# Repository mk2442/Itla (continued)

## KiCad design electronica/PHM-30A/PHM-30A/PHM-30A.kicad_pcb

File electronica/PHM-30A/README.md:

# PHM-30A
Puente H con Mosfet discretos 30A

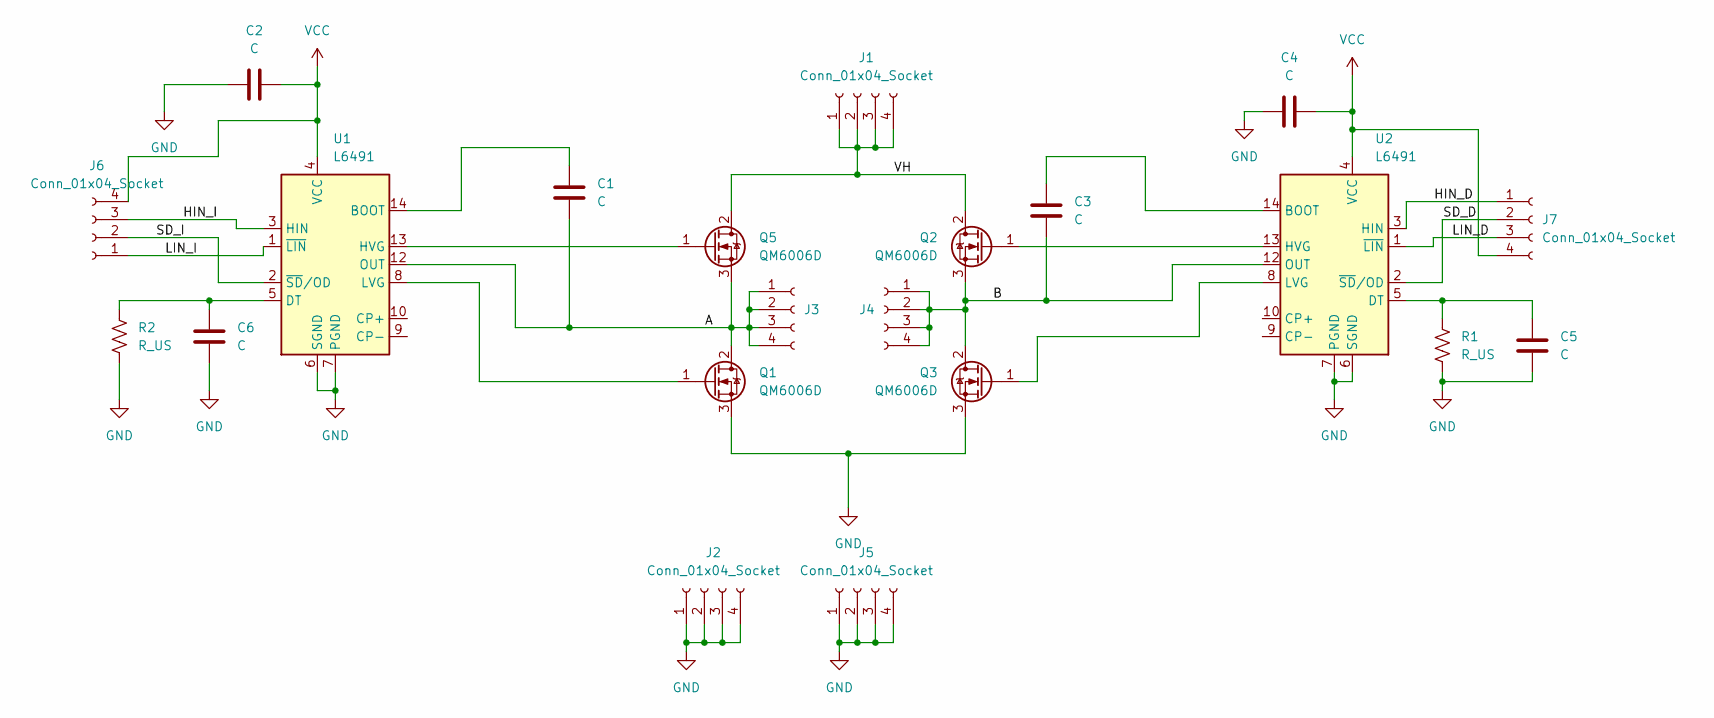
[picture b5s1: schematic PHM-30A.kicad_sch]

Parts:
C1, C2, C3, C4: C; C_0805_2012Metric
C5, C6: C; C_0603_1608Metric
J1, J2, J3, J4, J5, J6, J7: Conn_01x04_Socket; PinSocket_1x04_P1.27mm_Castellated
Q1, Q2, Q3, Q5: QM6006D; TO-252-2
R1, R2: R_US; R_0603_1608Metric
U1, U2: L6491; SO-14_3.9x8.65mm_P1.27mm

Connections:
/A: C1.2, J3.1, J3.2, J3.3, J3.4, Q1.2 (D), Q5.3 (S), U1.12 (OUT)
/B: C3.2, J4.1, J4.2, J4.3, J4.4, Q2.3 (S), Q3.2 (D), U2.12 (OUT)
/HIN_D: J7.1, U2.3 (HIN)
/HIN_I: J6.3, U1.3 (HIN)
/LIN_D: J7.3, U2.1 (~LIN)
/LIN_I: J6.1, U1.1 (~LIN)
/SD_D: J7.2, U2.2 (~SD/OD)
/SD_I: J6.2, U1.2 (~SD/OD)
/VH: J1.1, J1.2, J1.3, J1.4, Q2.2 (D), Q5.2 (D)
GND: C2.2, C4.1, C5.1, C6.1, J2.1, J2.2, J2.3, J2.4, J5.1, J5.2, J5.3, J5.4, Q1.3 (S), Q3.3 (S), R1.2, R2.2, U1.6 (SGND), U1.7 (PGND), U2.6 (SGND), U2.7 (PGND)
unnamed: Q1.1 (G), U1.8 (LVG)
unnamed: Q2.1 (G), U2.13 (HVG)
unnamed: Q3.1 (G), U2.8 (LVG)
unnamed: Q5.1 (G), U1.13 (HVG)
unnamed: C1.1, U1.14 (BOOT)
unnamed: C6.2, R2.1, U1.5 (DT)
unnamed: C3.1, U2.14 (BOOT)
unnamed: C5.2, R1.1, U2.5 (DT)
VCC: C2.1, C4.2, J6.4, J7.4, U1.4 (VCC), U2.4 (VCC)

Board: 2 copper layers, 21 parts (0 on the bottom side), 19 nets, no tracks yet.

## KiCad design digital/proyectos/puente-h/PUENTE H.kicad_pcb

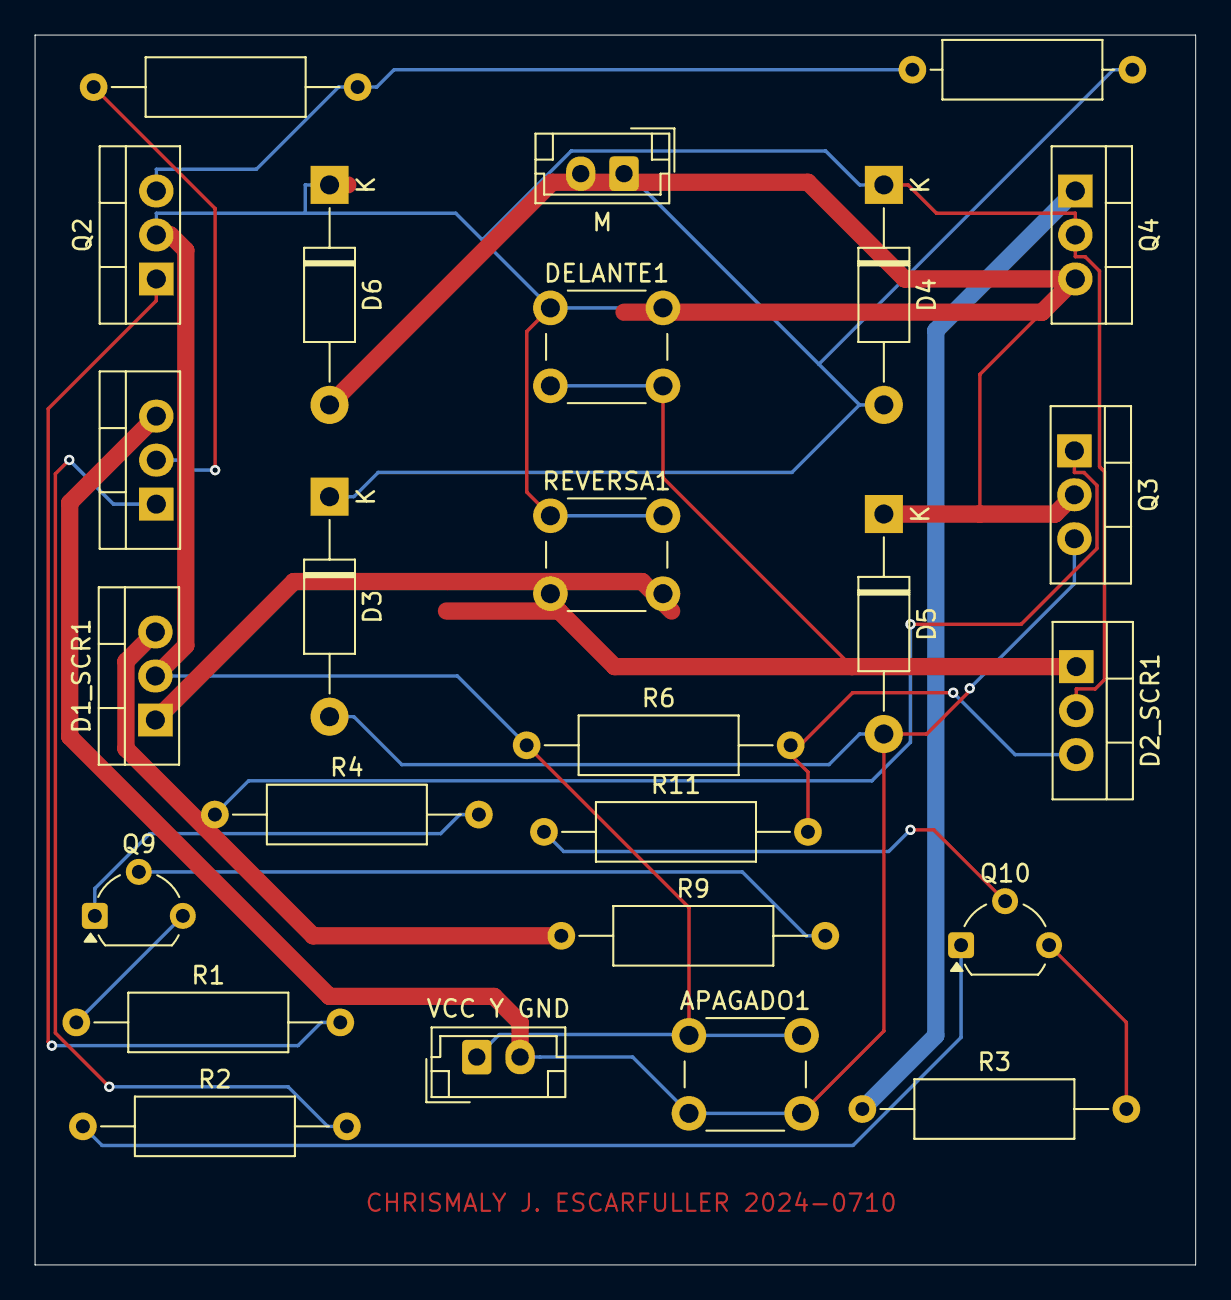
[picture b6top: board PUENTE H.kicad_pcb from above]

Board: 2 copper layers, 67.0 x 71.0 mm, 26 parts (0 on the bottom side), 20 nets.

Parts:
APAGADO1: SW_Push; SW_PUSH_6mm_H7.3mm
D1_SCR1, D2_SCR1: Q_SCR_GAK; TO-220-3_Vertical
D3, D4, D5, D6: 1N4007; D_DO-41_SOD81_P12.70mm_Horizontal
DELANTE1: SW_Push; SW_PUSH_6mm_H7.3mm
M: Screw_Terminal_01x02; JST_EH_B2B-EH-A_1x02_P2.50mm_Vertical
Q1, Q2, Q3, Q4: TIP41; TO-220-3_Vertical
Q9, Q10: 2N3904; TO-92L_Wide
R1, R2, R3, R4, R6, R9, R11: R; R_Axial_DIN0309_L9.0mm_D3.2mm_P15.24mm_Horizontal
REVERSA1: SW_Push; SW_PUSH_6mm_H7.3mm
VCC Y GND: Screw_Terminal_01x02; JST_EH_B2B-EH-A_1x02_P2.50mm_Vertical
jUMPER1: R; R_Axial_DIN0309_L9.0mm_D3.2mm_P12.70mm_Horizontal
jUMPER2: R; R_Axial_DIN0309_L9.0mm_D3.2mm_P15.24mm_Horizontal

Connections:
GNDPWR: APAGADO1.2, D3.2 (A), D5.2 (A), Q1.3 (E), Q3.3 (E), VCC Y GND.2
unnamed: D1_SCR1.1 (G), REVERSA1.2
unnamed: D1_SCR1.3 (K), R9.1
unnamed: D2_SCR1.1 (G), DELANTE1.2
unnamed: D2_SCR1.3 (K), R6.2, R11.2
unnamed: D3.1 (K), D4.2 (A), M.1, jUMPER1.2
unnamed: D5.1 (K), D6.2 (A), M.2, Q3.2 (C), Q4.3 (E)
unnamed: Q1.1 (B), R2.2
unnamed: Q1.2 (C), jUMPER2.1
unnamed: Q2.1 (B), R1.2
unnamed: Q2.3 (E), jUMPER1.1, jUMPER2.2
unnamed: Q3.1 (B), R4.1
unnamed: Q4.1 (B), R3.1
unnamed: Q9.2 (B), R9.2
unnamed: Q9.3 (C), R1.1
unnamed: Q9.1 (E), R4.2
unnamed: Q10.2 (B), R11.1
unnamed: Q10.3 (C), R3.2
unnamed: Q10.1 (E), R2.1
VCC: APAGADO1.1, D1_SCR1.2 (A), D2_SCR1.2 (A), D4.1 (K), D6.1 (K), DELANTE1.1, Q2.2 (C), Q4.2 (C), R6.1, REVERSA1.1, VCC Y GND.1

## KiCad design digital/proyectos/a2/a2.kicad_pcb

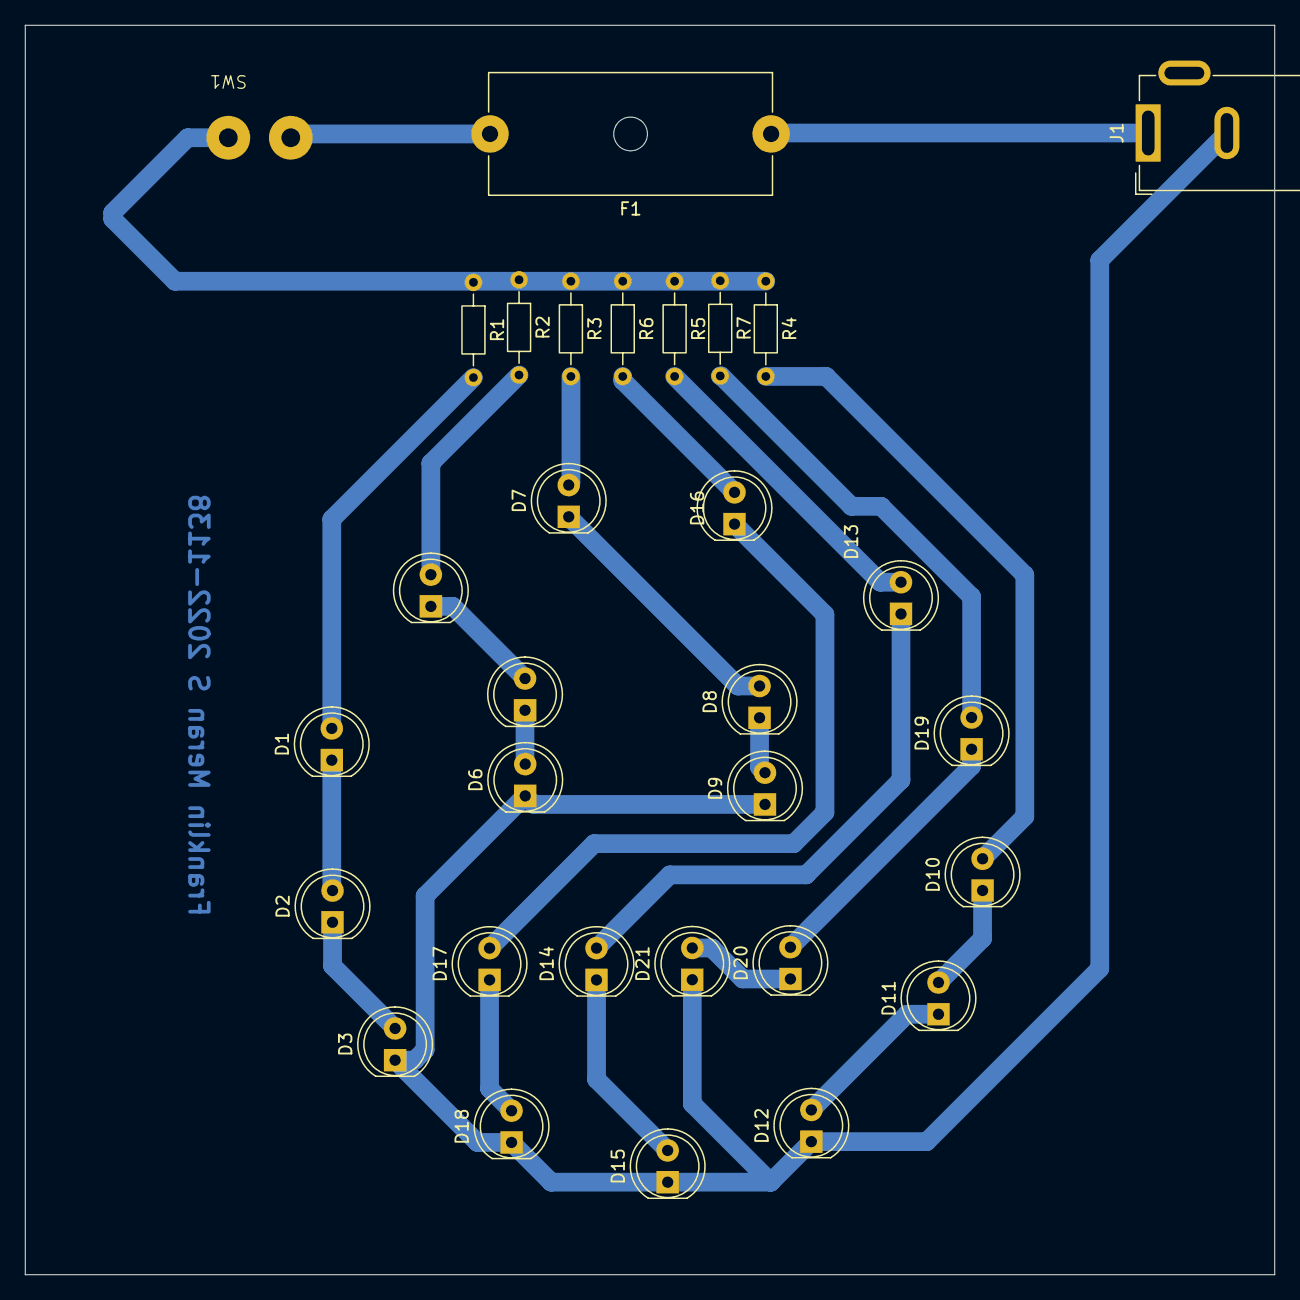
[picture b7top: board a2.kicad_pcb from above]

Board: 2 copper layers, 100.0 x 100.0 mm, 31 parts (0 on the bottom side), 25 nets.

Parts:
D1, D2, D3, D4, D5, D6, D7, D8, D9, D10, D11, D12, D13, D14, D15, D16, D17, D18, D19, D20, D21: LED; LED_D5.0mm_Clear
F1: Fuse; Fuseholder_Cylinder-5x20mm_Schurter_0031_8201_Horizontal_Op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
J1: Jack-DC; BarrelJack_GCT_DCJ200-10-A_Horizontal
R1, R2, R3, R4, R5, R6, R7: R; R_Axial_DIN0204_L3.6mm_D1.6mm_P7.62mm_Horizontal
SW1: SW_DIP_x01; Untitled

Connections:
unnamed: D1.2 (A), R1.2
unnamed: D1.1 (K), D2.2 (A)
unnamed: D2.1 (K), D3.2 (A)
unnamed: D4.2 (A), R2.2
unnamed: D4.1 (K), D5.2 (A)
unnamed: D5.1 (K), D6.2 (A)
unnamed: D7.2 (A), R3.2
unnamed: D7.1 (K), D8.2 (A)
unnamed: D8.1 (K), D9.2 (A)
unnamed: D10.2 (A), R4.2
unnamed: D10.1 (K), D11.2 (A)
unnamed: D11.1 (K), D12.2 (A)
unnamed: D3.1 (K), D6.1 (K), D9.1 (K), D12.1 (K), D15.1 (K), D18.1 (K), D21.1 (K), J1.2
unnamed: D13.2 (A), R5.2
unnamed: D13.1 (K), D14.2 (A)
unnamed: D14.1 (K), D15.2 (A)
unnamed: D16.2 (A), R6.2
unnamed: D16.1 (K), D17.2 (A)
unnamed: D17.1 (K), D18.2 (A)
unnamed: D19.2 (A), R7.2
unnamed: D19.1 (K), D20.2 (A)
unnamed: D20.1 (K), D21.2 (A)
unnamed: F1.2, SW1.1
unnamed: F1.1, J1.1
unnamed: R1.1, R2.1, R3.1, R4.1, R5.1, R6.1, R7.1, SW1.2

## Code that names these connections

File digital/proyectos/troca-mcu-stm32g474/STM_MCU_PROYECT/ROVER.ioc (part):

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Mcu.Name=STM32G474V(B-C-E)Tx
Mcu.Package=LQFP100
Mcu.UserName=STM32G474VETx
PA0.Signal=S_TIM2_CH1
PA1.Signal=S_TIM2_CH2
PA10.GPIOParameters=GPIO_Label
PA10.GPIO_Label=G_SEL_0
PA10.Signal=GPIO_Output
PA11.GPIOParameters=GPIO_Label
PA11.GPIO_Label=G_SEL_1
PA11.Signal=GPIO_Output
PA12.Signal=S_TIM4_CH2
PA13.Mode=Serial_Wire
PA13.Signal=SYS_JTMS-SWDIO
PA14.Mode=Serial_Wire
PA14.Signal=SYS_JTCK-SWCLK
PA15.GPIOParameters=GPIO_Label
PA15.GPIO_Label=MUX_SEL0
PA15.Signal=GPIO_Output
PA2.Signal=S_TIM2_CH3
PA3.Signal=S_TIM2_CH4
PA4.Signal=S_TIM3_CH2
PA6.Signal=S_TIM3_CH1
PB0.GPIOParameters=GPIO_Label
PB0.GPIO_Label=MUX_SEL1
PB0.Signal=GPIO_Output
PB1.GPIOParameters=GPIO_Label
PB1.GPIO_Label=MUX_SEL1
PB1.Signal=GPIO_Output
PB10.Mode=Synchronous
PB10.Signal=USART3_TX
PB11.Mode=Synchronous
PB11.Signal=USART3_RX
PB12.Mode=Synchronous
PB12.Signal=USART3_CK
PB13.GPIOParameters=GPIO_Label
PB13.GPIO_Label=MUX_EN
PB13.Signal=GPIO_Output
PB14.Mode=IN5-Single-Ended
PB14.Signal=ADC1_IN5
PB2.Signal=S_TIM5_CH1
PB3.Mode=Full_Duplex_Master
PB3.Signal=SPI1_SCK
PB4.Mode=Full_Duplex_Master
PB4.Signal=SPI1_MISO
PB5.Mode=Full_Duplex_Master
PB5.Signal=SPI1_MOSI
PB6.GPIOParameters=GPIO_Label
PB6.GPIO_Label=CS/SS_0
PB6.Signal=GPIO_Output
PB7.GPIOParameters=GPIO_Label
PB7.GPIO_Label=CS/SS_1
PB7.Signal=GPIO_Output
PC0.Signal=S_TIM1_CH1
PC1.Signal=S_TIM1_CH2
PC12.Signal=S_TIM5_CH2
PC2.Signal=S_TIM1_CH3
PC3.Signal=S_TIM1_CH4
PC4.GPIOParameters=GPIO_Label
PC4.GPIO_Label=RF_DOUT_0
PC4.Signal=GPIO_Output
PC5.GPIOParameters=GPIO_Label
PC5.GPIO_Label=RF_EN
PC5.Signal=GPIO_Output
PC6.Signal=S_TIM8_CH1
PC7.Signal=S_TIM8_CH2
PC8.Signal=S_TIM8_CH3
PC9.Signal=S_TIM8_CH4
PD0.GPIOParameters=GPIO_Label
PD0.GPIO_Label=MOTOR4_INA
PD0.Signal=GPIO_Output
PD1.GPIOParameters=GPIO_Label
PD1.GPIO_Label=MOTOR4_INB
PD1.Signal=GPIO_Output
PD10.Signal=GPIO_Input
PD11.GPIOParameters=GPIO_Label
PD11.GPIO_Label=RF_DIN_0
PD11.Signal=GPIO_Input
PD12.Signal=S_TIM4_CH1
PD13.Mode=IN10-Single-Ended
PD13.Signal=ADC3_IN10
PD14.Signal=S_TIM4_CH3
PD15.Signal=S_TIM4_CH4
PD2.GPIOParameters=GPIO_Label
PD2.GPIO_Label=MOTOR5_INA
PD2.Signal=GPIO_Output
PD3.GPIOParameters=GPIO_Label
PD3.GPIO_Label=MOTOR5_INB
PD3.Signal=GPIO_Output
PD4.GPIOParameters=GPIO_Label
PD4.GPIO_Label=MOTOR6_INA
PD4.Signal=GPIO_Output
PD5.Signal=GPIO_Output
PD6.GPIOParameters=GPIO_Label
PD6.GPIO_Label=MOTOR7_INA
PD6.Signal=GPIO_Output
PD7.GPIOParameters=GPIO_Label
PD7.GPIO_Label=MOTOR7_INB
PD7.Signal=GPIO_Output
PD8.GPIOParameters=GPIO_Label
PD8.GPIO_Label=MOTOR8_INA
PD8.Signal=GPIO_Output
PD9.GPIOParameters=GPIO_Label
PD9.GPIO_Label=MOTOR8_INB
PD9.Signal=GPIO_Output
PE1.Signal=S_TIM20_CH4
PE10.GPIOParameters=GPIO_Label
PE10.GPIO_Label=MOTOR1_INB
PE10.Signal=GPIO_Output
PE11.GPIOParameters=GPIO_Label
PE11.GPIO_Label=MOTOR2_INA
PE11.Signal=GPIO_Output
PE12.GPIOParameters=GPIO_Label
PE12.GPIO_Label=MOTOR2_INB
PE12.Signal=GPIO_Output
PE13.GPIOParameters=GPIO_Label
PE13.GPIO_Label=MOTOR3_INA
PE13.Signal=GPIO_Output
PE14.GPIOParameters=GPIO_Label
PE14.GPIO_Label=MOTOR3_INB
PE14.Signal=GPIO_Output
PE2.Signal=S_TIM20_CH1
PE3.Signal=S_TIM20_CH2
PE4.Signal=S_TIM3_CH3
PE5.Signal=S_TIM3_CH4
PE8.Signal=S_TIM5_CH3
PE9.GPIOParameters=GPIO_Label
PE9.GPIO_Label=MOTOR1_INA
PE9.Signal=GPIO_Output
PF0-OSC_IN.Mode=HSE-External-Oscillator
PF0-OSC_IN.Signal=RCC_OSC_IN
PF1-OSC_OUT.Mode=HSE-External-Oscillator
PF1-OSC_OUT.Signal=RCC_OSC_OUT
PF2.Signal=S_TIM20_CH3
PF9.Signal=S_TIM5_CH4
RCC.HSE_VALUE=8000000
RCC.SYSCLKFreq_VALUE=16000000
board=custom
